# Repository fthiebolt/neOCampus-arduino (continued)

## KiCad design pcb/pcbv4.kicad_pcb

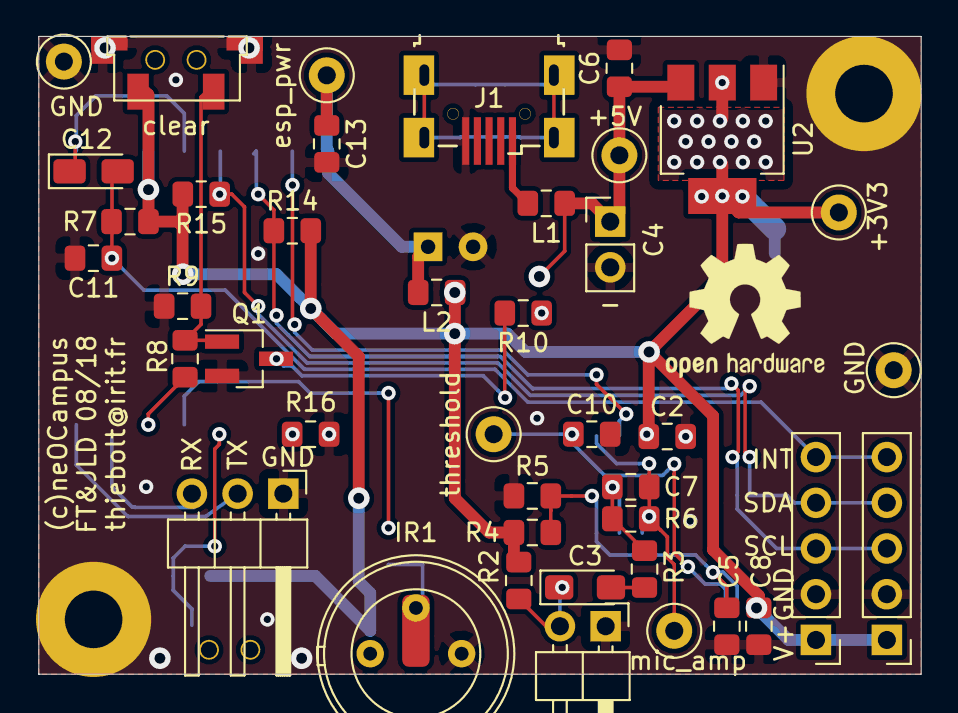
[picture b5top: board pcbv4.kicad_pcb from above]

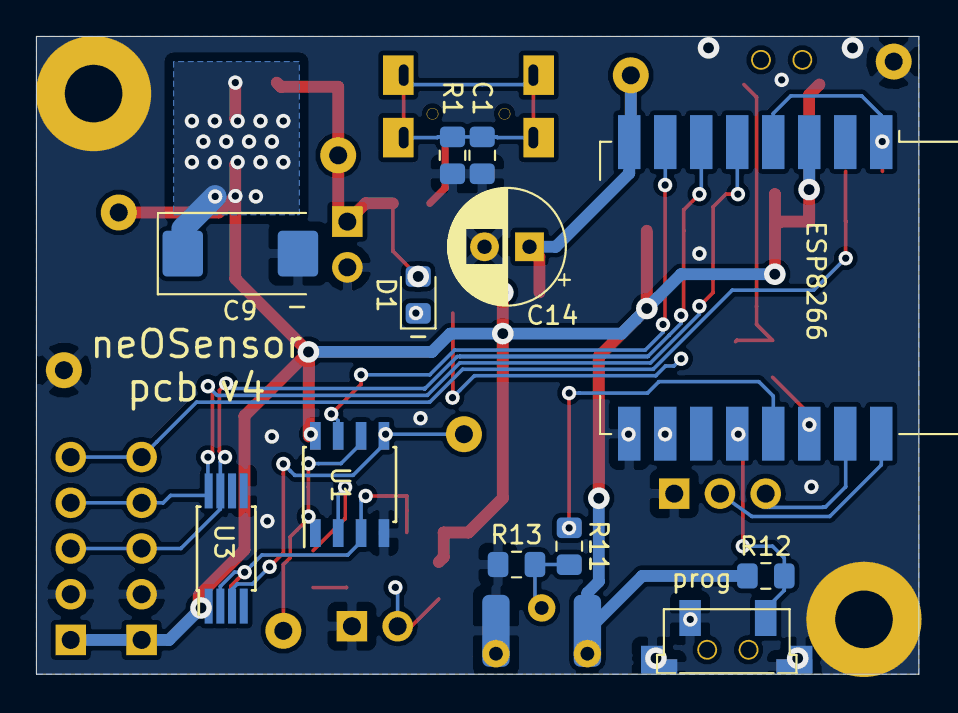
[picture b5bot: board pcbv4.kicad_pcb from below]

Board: 2 copper layers, 49.0 x 35.4 mm, 55 parts (12 on the bottom side), 27 nets.

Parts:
+3V3: +3v3; TestPoint_Loop_D2.50mm_Drill1.0mm
+5V: +5v; TestPoint_Loop_D2.50mm_Drill1.0mm
C1: 4n7; C_0805_2012Metric_Pad1.15x1.40mm_HandSolder
C2, C5, C8, C10, C11: 100n; C_0805_2012Metric_Pad1.15x1.40mm_HandSolder
C3: 1µ tantale; CP_EIA-3216-18_Kemet-A_Pad1.58x1.35mm_HandSolder
C4: 10µF (opt); PinHeader_1x02_P2.54mm_Vertical
C6, C13: 100nF; C_0805_2012Metric_Pad1.15x1.40mm_HandSolder
C7: 120p; C_0805_2012Metric_Pad1.15x1.40mm_HandSolder
C9: 220µF 6.3v; CP_EIA-7343-31_Kemet-D_Pad2.25x2.55mm_HandSolder
C12: 100nF to 1µF*; CP_EIA-3216-12_Kemet-S_Pad1.58x1.35mm_HandSolder
C14: 470µ 6.3v; CP_Radial_D6.3mm_P2.50mm
D1: Red; LED_0805_2012Metric_Pad1.15x1.40mm_HandSolder
ESP8266: ESP-12F-nospi
GND: GND; TestPoint_Loop_D2.50mm_Drill1.0mm
GND#2: GND; TestPoint_Loop_D2.50mm_Drill1.0mm
IR1: IRsensor; IRsensor_TH_and_smd
J1: USB_B_Micro; micro-usb-aliexpress
J2, J3: Conn_01x05; PinHeader_1x05_P2.54mm_Vertical
J4: Conn_01x03; PinHeader_1x03_P2.54mm_Horizontal
L1, L2: Ferrite 470R; R_0805_2012Metric_Pad1.15x1.40mm_HandSolder
MH1, MH2: 3.2mm for M3 screw; MountingHole_3.2mm_M3_Pad
MK1: Microphone; PinHeader_1x02_P2.54mm_Horizontal
Q1: 2N7002; SOT-23_Handsoldering
R1: 1M; R_0805_2012Metric_Pad1.15x1.40mm_HandSolder
R2: 2K; R_0805_2012Metric_Pad1.15x1.40mm_HandSolder
R3: 1K; R_0805_2012Metric_Pad1.15x1.40mm_HandSolder
R4, R5, R7, R12: 10K; R_0805_2012Metric_Pad1.15x1.40mm_HandSolder
R6: 100K; R_0805_2012Metric_Pad1.15x1.40mm_HandSolder
R8, R16: 470; R_0805_2012Metric_Pad1.15x1.40mm_HandSolder
R9, R13: 15K; R_0805_2012Metric_Pad1.15x1.40mm_HandSolder
R10: 68; R_0805_2012Metric_Pad1.15x1.40mm_HandSolder
R11: 330; R_0805_2012Metric_Pad1.15x1.40mm_HandSolder
R14, R15: 4K7; R_0805_2012Metric_Pad1.15x1.40mm_HandSolder
U1: AD8052; SOIC-8_3.9x4.9mm_P1.27mm
U2: AMS1117-3.3; SOT-223-3_TabPin2
U3: MCP47FEB21; TSSOP-8_4.4x3mm_P0.65mm_handsolder
clear: clear; G71Y_µsw_smd
esp_pwr: esp_pwr; TestPoint_Loop_D2.50mm_Drill1.0mm
mic_amp: MIC_AMP; TestPoint_Loop_D2.50mm_Drill1.0mm
prog: prog; G71Y_µsw_smd
threshold: Threshold; TestPoint_Loop_D2.50mm_Drill1.0mm

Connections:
+3V3: +3V3.1, C2.2, C8.2, C9.1, ESP8266.3, IR1.1, J2.1, J3.1, L2.2, R2.1, R4.1, R7.1, R12.1, R14.2, R15.2, U1.8, U2.2, U3.1, clear.1
+5V: +5V.1, C4.1, C6.1, D1.2, L1.1, U2.3
/GPIO0: ESP8266.18, R12.2, prog.1
/INT: C11.1, C12.2, J2.5, J3.5, R7.2
/IR: ESP8266.19, R11.2
/LED: ESP8266.20, R8.2
/NOISE: ESP8266.7, U1.7
/RST: C12.1, ESP8266.1, ESP8266.4
/RxD: ESP8266.21, J4.3
/SCL: ESP8266.6, J2.3, J3.3, R14.1, U3.7
/SDA: ESP8266.5, J2.4, J3.4, R15.1, U3.8
/TxD: ESP8266.22, J4.2
/esp_pwr: C13.1, C14.1, ESP8266.8, L2.1, esp_pwr.1
GND: C1.2, C2.1, C4.2, C5.2, C6.2, C8.1, C9.2, C10.2, C11.2, C13.2, C14.2, ESP8266.15, GND.1, GND#2.1, IR1.3, J1.5, J2.2, J3.2, J4.1, MH1.1, MH2.1, MK1.1, Q1.2, R1.2, R5.2, R9.1, R13.1, R16.1, U1.4, U2.1, U3.5, U3.6, clear.3, prog.2, prog.3
unnamed: C1.1, J1.6, R1.1
unnamed: C3.1, MK1.2, R2.2
unnamed: C3.2, R3.2
unnamed: C5.1, R4.2, R5.1, U1.3, U3.2
unnamed: C7.1, R6.1, U1.1, U1.6, mic_amp.1
unnamed: C7.2, R3.1, R6.2, U1.2
unnamed: C10.1, U1.5, U3.3, threshold.1
unnamed: D1.1, R10.1
unnamed: IR1.2, R11.1, R13.2
unnamed: J1.1, L1.2
unnamed: Q1.1, R8.1, R9.2, clear.2
unnamed: Q1.3, R10.2
unnamed: ESP8266.16, R16.2

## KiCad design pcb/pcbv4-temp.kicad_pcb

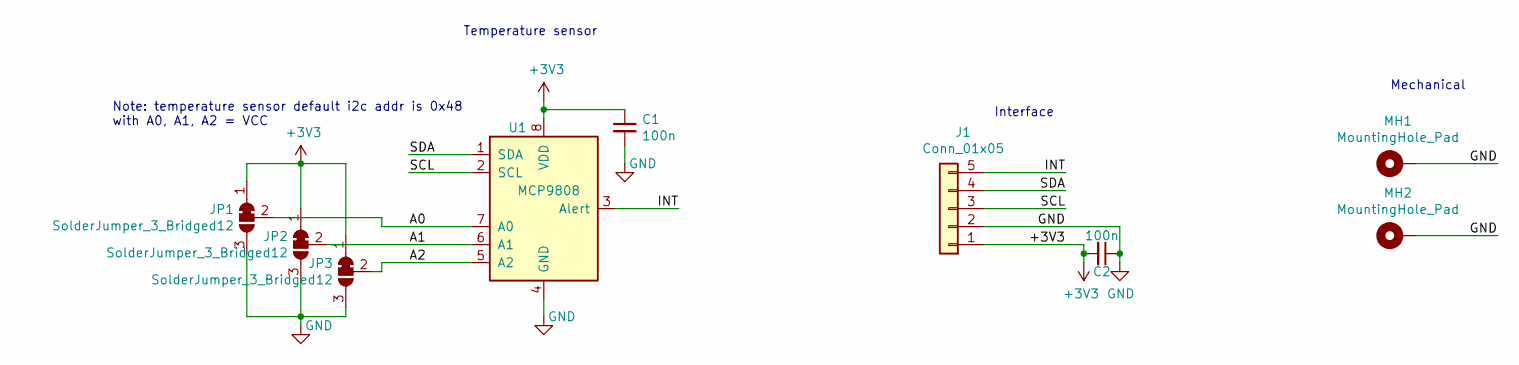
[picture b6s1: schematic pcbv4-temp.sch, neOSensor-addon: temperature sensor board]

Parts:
C1, C2: 100n; C_0805_2012Metric_Pad1.15x1.40mm_HandSolder
J1: Conn_01x05; PinHeader_1x05_P2.54mm_Vertical
JP1, JP2, JP3: SolderJumper_3_Bridged12; SolderJumper-3_P1.3mm_Bridged12_Pad1.0x1.5mm
MH1, MH2: MountingHole_Pad; MountingHole_3.2mm_M3_Pad
U1: MCP9808; MSOP-8_3x3mm_P0.65mm

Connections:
+3V3: C1.1, C2.2, J1.1, JP1.1 (A), JP2.1 (A), JP3.1 (A), U1.8 (VDD)
/A0: JP1.2 (C), U1.7 (A0)
/A1: JP2.2 (C), U1.6 (A1)
/A2: JP3.2 (C), U1.5 (A2)
/INT: J1.5, U1.3 (Alert)
/SCL: J1.3, U1.2 (SCL)
/SDA: J1.4, U1.1 (SDA)
GND: C1.2, C2.1, J1.2, JP1.3 (B), JP2.3 (B), JP3.3 (B), MH1.1, MH2.1, U1.4 (GND)

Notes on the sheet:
Temperature sensor
Interface
Note: temperature sensor default i2c addr is 0x48 with A0, A1, A2 = VCC
Mechanical

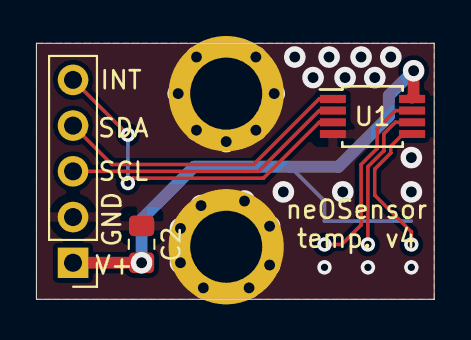
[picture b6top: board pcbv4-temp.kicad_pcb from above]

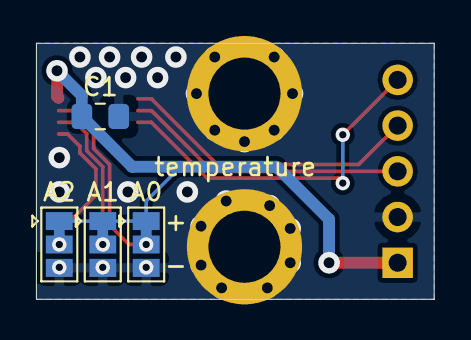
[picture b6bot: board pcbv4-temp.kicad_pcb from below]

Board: 2 copper layers, 22.1 x 14.2 mm, 9 parts (4 on the bottom side), 8 nets.

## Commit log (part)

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2020-08-24 added regular neOSensor board. sensOCampus JSON config is working.
2020-08-24 Update README.md
    some minor corrections
2020-08-26 start to add support for ESP32 ADC calibration
2020-08-27 strating to enable advanced adc ops on esp32
2020-09-04 full lcc_sensor driver
2020-09-08 switched esp8266 from QIO to DIO flash mode
2020-09-10 corrected wront unitID for deviceModule
2020-09-18 force SDK 2.7.1 for esp8266
2020-09-23 new Rsensor computation proposal
2020-11-02 corrected force float values for temperatire and airquality
2020-11-06 MAX44009 on way
2020-11-09 updated with fakes MAX44009...
2020-11-09 use LED when SYS_LED not available
2020-11-10 start of SSD1306 display driver
2020-11-10 added IRIT ntp server; added neOClock support
2021-01-04 update repo structure for future pcb-v5
2021-02-03 started pcb v5
2021-02-04 updated ignored files
2021-02-04 updated neOSensorV5 pcb
2021-02-04 update pcb v5
2021-02-05 update neOSensor V5
2021-02-07 added analog inputs to pcb v5
2021-02-10 added nodes labels and minor corrections to pcb v5
2021-02-10 panelized PCB V5 ready for manufacturing
2021-02-11 undertaking some cleanup ...
2021-02-12 preliminary support for LoRaWAN CubeCell modules
2021-02-12 tweaked neOSensor-lorawan arduino menu
2021-02-12 minor fix in arduino menu for lorawan neOSensor
2021-02-13 trying U8g2 library for our future displays ...
2021-02-17 added TODO notes about PCB-v5
2021-03-31 added initial support to neOSensor PCB v5 :)
2021-03-31 start mods for pcb v5.1
2021-03-31 update neOSensorV5 schematic
2021-04-02 updated pcb v5 layout
2021-04-02 new neOSensor V5.1 PCB done :)
2021-04-04 prepare migration to esp32 1.0.6
2021-04-05 libs update, MQTT API for settings, move to esp32 1.0.6
2021-04-07 added sntp callback for ESP32
2021-04-13 added esp32 flag for NTP from DHCP server
2021-04-13 extended MAX44009 detection capabilities
2021-04-13 added pics from neOSensorV5 final view
2021-04-14 added neOSensorV5 pics
2021-04-16 first try to get NTP server from DHCP answer
2021-04-20 news for NTP extended support in LWIP
2021-05-21 added preliminary support for our own kicad libs
2021-05-21 add lib in kicad-lib & add neOClock
2021-05-25 first neOClock pcb along with lorawan
2021-05-26 added original neOSensor-lorawan pcb ... then create lorawan-v2
2021-05-27 corrected ATCC508 and some others from neOSensor_addon
2021-05-28 HTCC-AB02 integration
2021-05-28 corrected SAA1064
2021-06-01 mise a jour des schema
2021-06-03 HTCC-AB01 on way to get corrected
2021-06-04 updated HTCC-AB01 footprint
2021-06-09 lorawanV2 schematic is ok. PCB is on way
2021-06-09 lorawan-v2 pcb update
2021-06-10 neOSensor-LoRaWAN V2 ready for manfacturing
2021-06-14 maj schema + route
2021-06-24 added note for neOSensor pcb V5.2
2021-06-25 lorawanV2 docs update
2021-06-28 corrected link to CubeCell cross-compilation tools
2021-07-01 neOSensor LoRaWAN V2.1 pcb
2021-07-02 new LoRaWAN V2.1 sent to manufacturing
2021-07-05 comment about esp32/GPIO15 being high at boot
2021-07-05 added space invaders for M5stack
2021-08-12 on way for digitalModule ...
2021-08-20 on way to shared JSON for all modules own data
2021-08-24 temperature module now send data upon modification, sharedJSON structure updated
2021-08-24 modules tmperature, humidity and luminosity now send data upon data variation
2021-08-25 added data rounding to sensors and double i2c scan to improve detection
2021-08-25 extended deploy script with libraries extensions now automatically copied
2021-08-25 added limits.h for esp8266 compilation
2021-08-25 adding sensOCampus config for digital inputs
2021-08-25 new milestone reached :)
2021-08-26 added missing MAX_COOLDOWN_SENSOR feature activation
2021-08-26 added device status along with additional messages sent according to status change
2021-08-26 bug workaround for esp8266 targets about loadsensoconfig in digital and airquality modules ... investigations pending
2021-08-27 corrected esp8266 stack issue due to ways too large StaticJsonDocument
2021-08-29 on way to display module for oled displays :)
2021-09-05 improved oled display I2C detection
2021-09-05 first time display to work displaying time :)
2021-10-21 corrected first time format SPIFFS now subsequently mounted FS
2021-10-25 sht2x hunt for bug ...
2021-10-25 hunt for sht2x bug
2021-10-25 sht2x humidity bug hunt
2021-10-26 disabling TEMPERATURE_CORRECTION_LASTI2C
2021-10-26 sht2x driver corrected
2021-10-26 release 211026
2021-10-26 airquality serial sensor is on way
2021-10-27 on way to serial particule meter
2021-10-28 sample PMS5003 code update
2021-10-31 added PMS library along with test sample code
2021-10-31 pms_serial sensor is on way
2021-11-01 pms_serial driver is on way
2021-11-03 added support for multiple values,subIDs and sensorUnits to get sent back from a single sensor
2021-11-03 airquality lcc_sensor converted to data driven behaviour ... tests needed
2021-11-03 pm_serial driver is on way
2021-11-04 corrected TZ for esp32 with daylights savings now working
2021-11-05 pm_serial is on way
2021-11-05 preliminary support for single airquality sensor sending back multiple values and subIDs
2021-11-10 serial driver for PMs still on way
2021-11-10 PMSx003 serial sensors integrated :)
2021-11-19 added IKEA pm sensor :)
2021-11-19 added SDS011 PM sensor
2021-11-22 added powerSave option ==> disabling power save mode for SDS011 (noisy sensor)
2021-11-22 start to add airquality PM to get displayed
2021-11-26 on way to serial CO2 integration
2021-11-28 MHZ-1x integration done
2021-11-29 corrected airquality data sent while it didn t changed
2021-11-29 release with serial PMsensors and CO2 :)
2021-12-02 added DXF files for laser cutter
2021-12-03 added new LoRa-E5 from seeed and added new lasercut files
2021-12-09 corrected neOSensorV5 desktop case
2021-12-10 update stm32 link
2022-02-25 mod IKEA PM sensor with new command
2022-03-07 on way to Sensirion SDC4x i2c CO2+temp+hygro sensor
2022-03-13 SCD4x sensor is on way ...
2022-03-14 added temperature support for SCD4x
2022-03-15 trying to overcome i2c comm issues with TSL2561
2022-03-15 corrected TSL2561 detection with latest i2c primitives from neOCampus
2022-03-16 corrected multi-sensors corner case in general calls
2022-03-16 SCD4x integration is over --> sensor operational :)
2022-03-18 switch back to regular IKEA PMsensor commands + added hex_dump for frames
2022-03-28 save WiFi credentials typed by the user even if unable to connect to the GW
2022-03-29 workaround for Serial2 error when compiling for esp8266
2022-04-18 added SoftwareSerial port2 for esp8266 serial sensors. Tests required!
2022-08-08 updated boards definitions along with lwipV2 recompiled with DHCP support for NTP servers
2022-08-09 uniformized sntp calls for all ESPs :)
2022-08-09 updated libraries. Started to update code to match new APIs
2022-08-11 updated _http_get with WIFIClient newer API
2022-08-15 corrected boards definition for esp32
2022-08-16 missing return in function
2022-08-16 improved WiFi connection and no more WiFiManager mods required
2022-08-17 corrected display of currently used NTP server(s)
2022-09-07 myGates iBeacon first tests
2022-09-18 bump to ESP32 v2.0.5 with recompiled liblwip
2022-09-19 added new EraseFlash option to boards.local.txt
2022-09-23 added ESP32 AES hardware encyption and decrypt example
2022-11-28 advertise and scan for UUID
2022-11-29 add SCAN_STATE and OPEN_GATE_STATE
2022-11-29 add relay opening gate
2022-11-30 add #define thresholds and change gettime
2022-12-02 keep gates open by sending pulse
2022-12-06 add OTA with ESP32 in access point
2022-12-09 start OTA BLE tram
2022-12-13 set MAC address test
2023-01-04 with BLE scan asynch/non blocking
2023-01-09 disabled setMinimumSignalStrenght
2023-01-11 move to folder myGates and add wdt for BLE
2023-07-31 bumps to esp32 2.0.11
2023-10-03 lasercut on way to update
2023-10-26 added WiFi cred backup to NVS if not already set
2023-10-27 Realease 231027
2023-10-27 started new neOSensor 5B pcb
2023-10-28 updated neOSensor V5B schematic
2023-11-02 ThermoPro get temp/humidity
2023-12-06 get temperature update
2024-01-22 Update README.md move notification
